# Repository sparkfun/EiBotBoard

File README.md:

EiBotBoard
==========

[*EiBotBoard (WIG-10025)*](https://www.sparkfun.com/products/10025)

The EiBotBoard (EBB) was originally designed for the Egg-Bot project. 
It is a small (2.2" x 2.2") two channel stepper motor driver board with USB microcontroller. 
It is based on the UBW board and supports all of the commands that the UBW does (for the most part), plus several extra, like stepper motor commands and RC servo output commands.

Repository Contents
-------------------
* **/Hardware** - All Eagle design files (.brd, .sch)
* **/Production** - Production panel files (.brd)

License Information
-------------------
Distributed as-is; no warranty is given.

_**Note:** This product is a collaboration with Brian Schmalz. A portion of each sales goes back to him for product support and continued development._

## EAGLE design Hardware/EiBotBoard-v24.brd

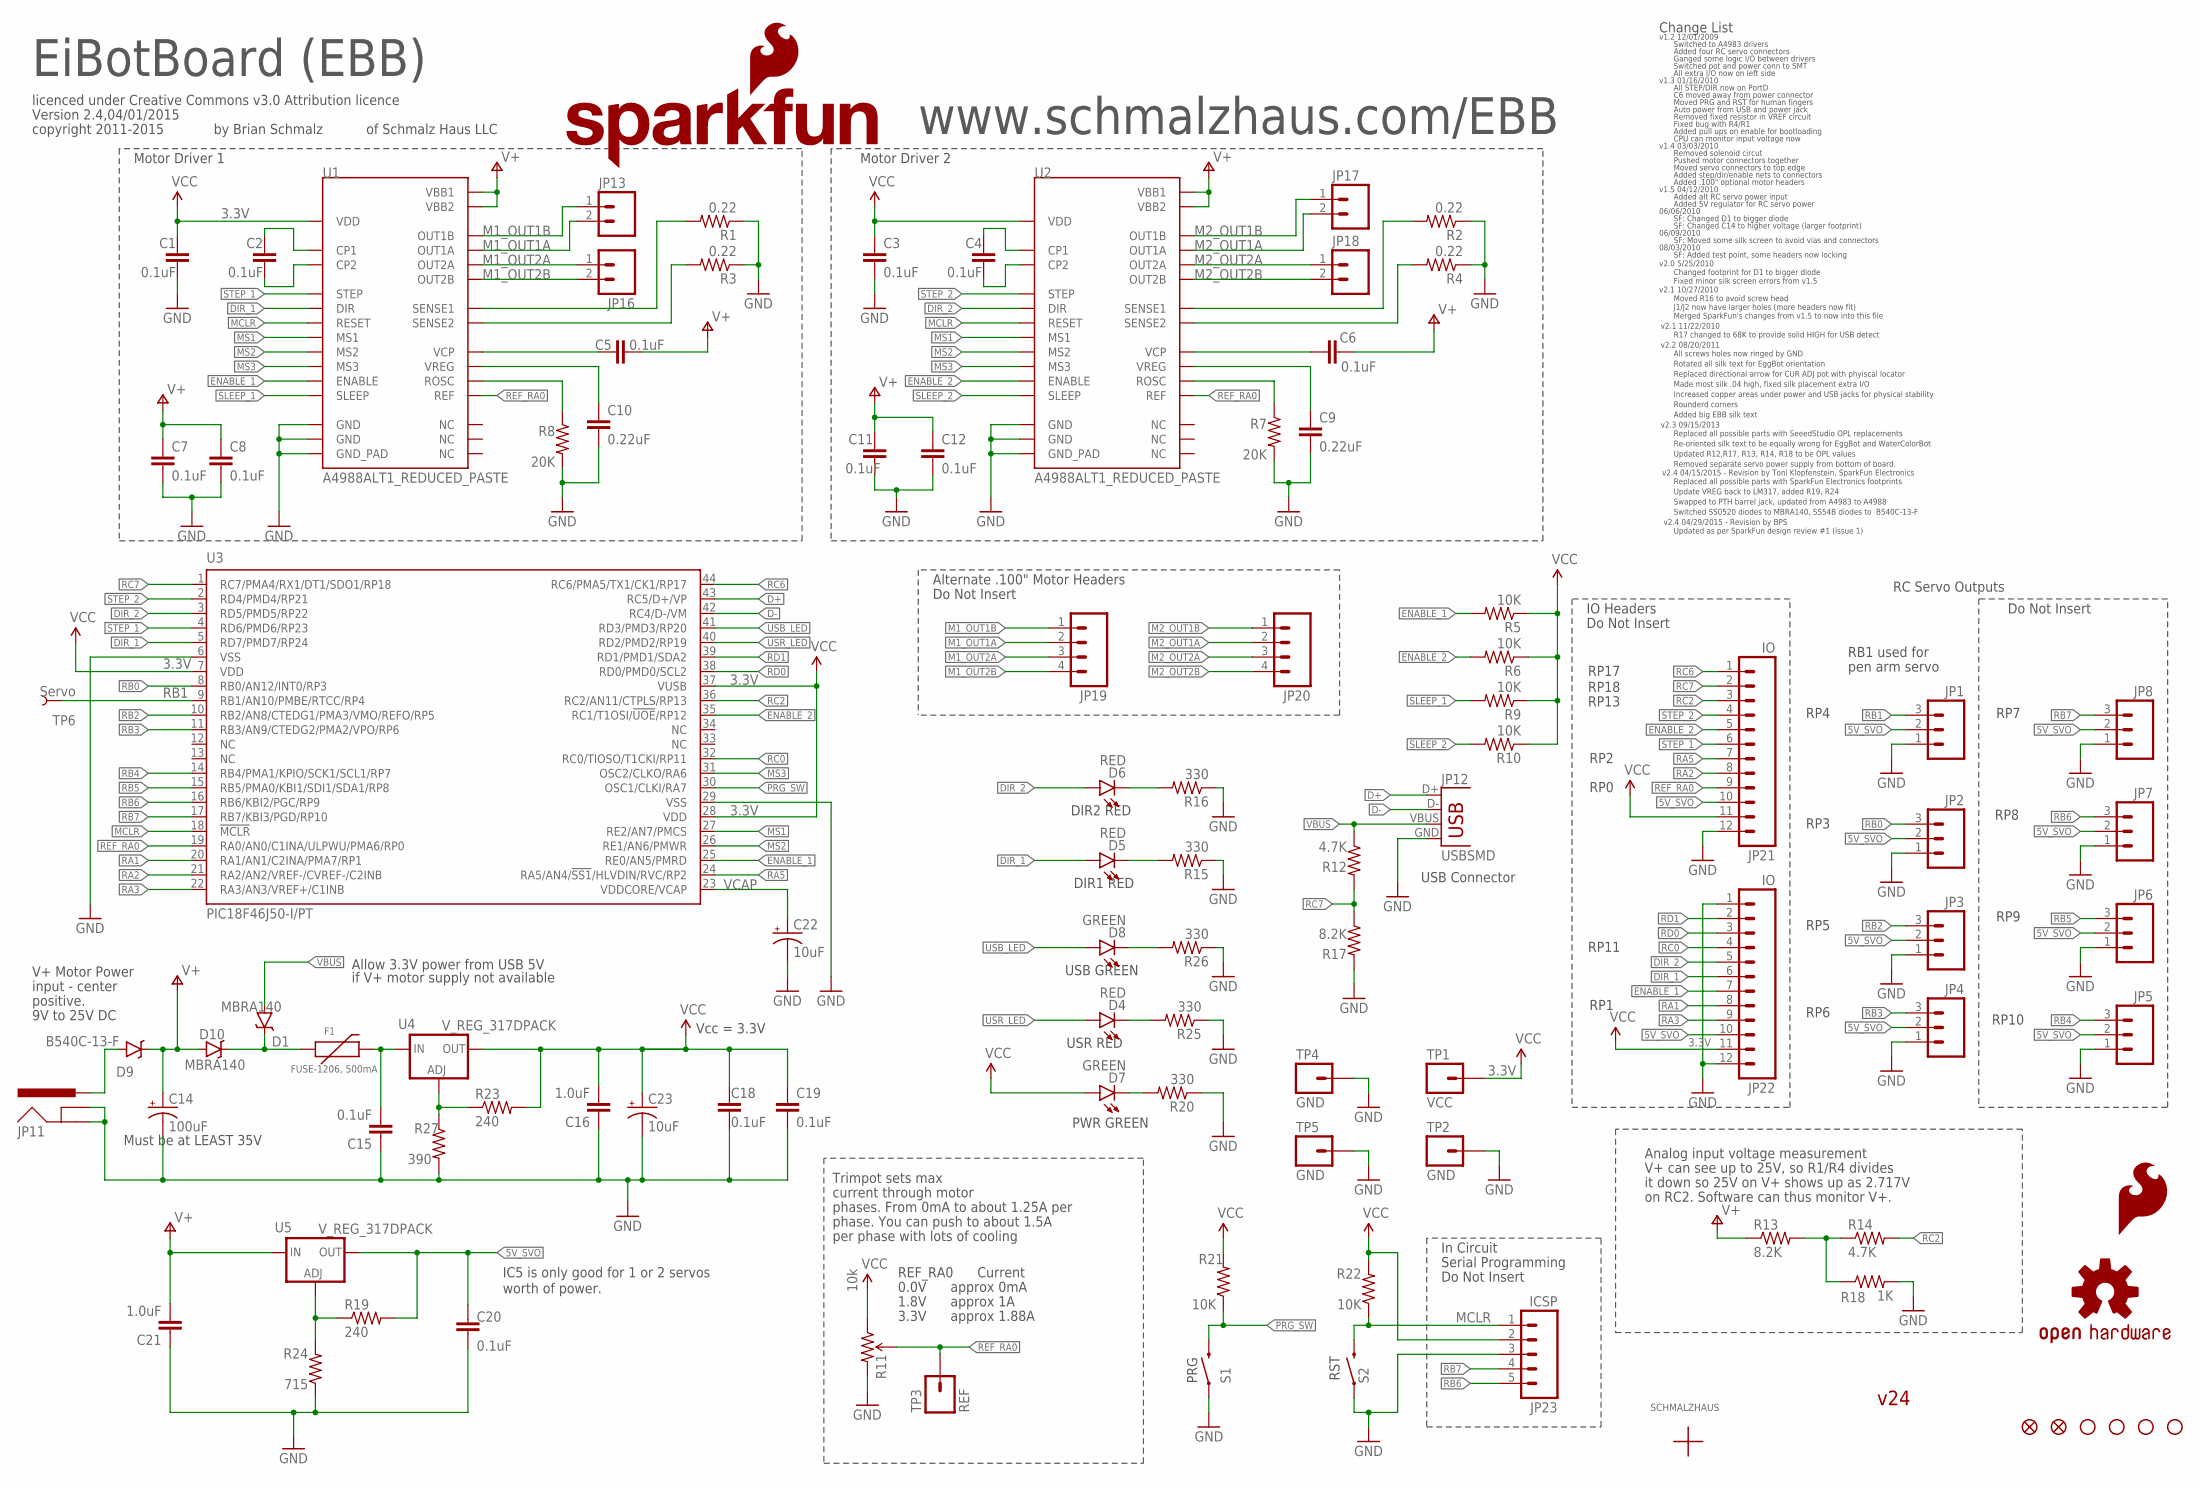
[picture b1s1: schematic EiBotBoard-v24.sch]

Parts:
C1, C2, C3, C4, C5, C6, C7, C8, C11, C12, C15, C18, C19, C20: 0.1uF; 0603-CAP
C9, C10: 0.22uF; 0603-CAP
C14: 100uF; NIC_10X10.5_CAP
C16, C21: 1.0uF; 0603-CAP
C22, C23: 10uF; EIA3528
D1, D10: MBRA140; SMA-DIODE
D4, D5, D6: RED; LED-0603
D7, D8: GREEN; LED-0603
D9: B540C-13-F; SMC
F1: FUSE-1206, 500mA; PTC-1206
JP1, JP2, JP3, JP4, JP5, JP6, JP7, JP8: M03LOCK_NO_SILK; 1X03_LOCK_NO_SILK
JP11: POWER_JACKPTH_LOCK; POWER_JACK_PTH_LOCK
JP12: USBSMD; USB-MINIB
JP13, JP16, JP17, JP18: M023.5MM_LOCK; SCREWTERMINAL-3.5MM-2_LOCK
JP14, JP15: FIDUCIAL1X2; FIDUCIAL-1X2
JP19, JP20: M04POLAR; MOLEX-1X4
JP21, JP22: IO; 1X12
JP23: ICSP; 1X05_NO_SILK
LOGO1: OSHW-LOGOS; OSHW-LOGO-S
LOGO2: SFE_LOGO_FLAME.2_INCH; SFE_LOGO_FLAME_.2
LOGO3: SFE_LOGO_NAME_FLAME.2_INCH; SFE_LOGO_NAME_FLAME_.2
R1, R2, R3, R4: 0.22; 0805
R5, R6, R9, R10, R21, R22: 10K; 0603-RES
R7, R8: 20K; 0603-RES
R11: 10k; TRIMPOT-3MM
R12, R14: 4.7K; 0603-RES
R13, R17: 8.2K; 0603-RES
R15, R16, R20, R25, R26: 330; 0603-RES
R18: 1K; 0603-RES
R19, R23: 240; 0603-RES
R24: 715; 0603-RES
R27: 390; 0603-RES
S1, S2: SWITCH-MOMENTARY-2SMD; TACTILE-SWITCH-SMD
TP1: VCC; 1X01_NOSILK
TP2, TP4, TP5: GND; 1X01_NOSILK
TP3: REF; 1X01
TP6: Servo; PAD.03X.05
U1, U2: A4988ALT1_REDUCED_PASTE; QFN-28-5MM_ALT1_REDUCED_PASTE
U3: PIC18F46J50-I/PT; TQFP44
U4, U5: V_REG_317DPACK; V-REG_DPACK
U$1: SCHMALZHAUSSCHMALZHAUS_SMALL; SCHMALZHAUS_SMALL
U$2, U$3, U$4, U$5: STAND-OFF

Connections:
3.3V: C1.1, C3.1, C16.2, C18.2, C19.2, C23.A (+), D7.A, JP21.11, JP22.11, JP23.2, R5.1, R6.1, R9.1, R10.1, R11.1 (CCW), R21.2, R22.2, R23.2, TP1.1, U1.P$15 (VDD), U2.P$15 (VDD), U3.7 (VDD), U3.28 (VDD), U3.37 (VUSB), U4.4 (OUT)
5V_SVO: C20.2, JP1.2, JP2.2, JP3.2, JP4.2, JP5.2, JP6.2, JP7.2, JP8.2, JP21.10, JP22.10, R19.2, U5.4 (OUT)
D+: JP12.D+, U3.43 (RC5/D+/VP)
D-: JP12.D-, U3.42 (RC4/D-/VM)
DIR_1: D5.A, JP22.6, U1.P$19 (DIR), U3.5 (RD7/PMD7/RP24)
DIR_2: D6.A, JP22.5, U2.P$19 (DIR), U3.3 (RD5/PMD5/RP22)
ENABLE_1: JP22.7, R5.2, U1.P$2 (ENABLE), U3.25 (RE0/AN5/PMRD)
ENABLE_2: JP21.5, R6.2, U2.P$2 (ENABLE), U3.35 (RC1/T1OSI/!UOE!/RP12)
GND: C1.2, C3.2, C7.2, C8.2, C9.2, C10.2, C11.2, C12.2, C14.-, C15.1, C16.1, C18.1, C19.1, C20.1, C21.1, C22.C (-), C23.C (-), JP1.1, JP2.1, JP3.1, JP4.1, JP5.1, JP6.1, JP7.1, JP8.1, JP11.GND, JP11.GNDBREAK, JP12.GND, JP21.12, JP22.1, JP22.12, JP23.3, R1.1, R2.1, R3.1, R4.1, R7.2, R8.2, R11.3 (CW), R15.1, R16.1, R17.2, R18.2, R20.1, R24.1, R25.1, R26.1, R27.2, S1.1, S2.1, TP2.1, TP4.1, TP5.1, U1.P$3 (GND), U1.P$18 (GND), U1.P$29 (GND_PAD), U2.P$3 (GND), U2.P$18 (GND), U2.P$29 (GND_PAD), U3.6 (VSS), U3.29 (VSS)
M1_OUT1A: JP13.2, JP19.2, U1.P$24 (OUT1A)
M1_OUT1B: JP13.1, JP19.1, U1.P$21 (OUT1B)
M1_OUT2A: JP16.1, JP19.3, U1.P$26 (OUT2A)
M1_OUT2B: JP16.2, JP19.4, U1.P$1 (OUT2B)
M2_OUT1A: JP17.2, JP20.2, U2.P$24 (OUT1A)
M2_OUT1B: JP17.1, JP20.1, U2.P$21 (OUT1B)
M2_OUT2A: JP18.1, JP20.3, U2.P$26 (OUT2A)
M2_OUT2B: JP18.2, JP20.4, U2.P$1 (OUT2B)
MCLR: JP23.1, R22.1, S2.3 (2), U1.P$12 (RESET), U2.P$12 (RESET), U3.18 (!MCLR!)
MS1: U1.P$9 (MS1), U2.P$9 (MS1), U3.27 (RE2/AN7/PMCS)
MS2: U1.P$10 (MS2), U2.P$10 (MS2), U3.26 (RE1/AN6/PMWR)
MS3: U1.P$11 (MS3), U2.P$11 (MS3), U3.31 (OSC2/CLKO/RA6)
unnamed: D6.C, R16.2
unnamed: D1.C, D10.C, F1.1
unnamed: C2.1, U1.P$4 (CP1)
unnamed: R13.2, R14.1, R18.1
unnamed: C2.2, U1.P$5 (CP2)
unnamed: D9.A, JP11.PWR
unnamed: D5.C, R15.2
unnamed: D8.C, R26.2
unnamed: R23.1, R27.1, U4.1 (ADJ)
unnamed: D4.C, R25.2
unnamed: D7.C, R20.2
unnamed: R19.1, R24.2, U5.1 (ADJ)
unnamed: C4.1, U2.P$4 (CP1)
unnamed: C4.2, U2.P$5 (CP2)
unnamed: R8.1, U1.P$13 (ROSC)
unnamed: C10.1, U1.P$8 (VREG)
unnamed: C5.1, U1.P$6 (VCP)
unnamed: R3.2, U1.P$27 (SENSE2)
unnamed: R1.2, U1.P$23 (SENSE1)
unnamed: C15.2, F1.2, U4.3 (IN)
unnamed: C6.1, U2.P$6 (VCP)
unnamed: R2.2, U2.P$23 (SENSE1)
unnamed: R4.2, U2.P$27 (SENSE2)
unnamed: C9.1, U2.P$8 (VREG)
unnamed: R7.1, U2.P$13 (ROSC)
PRG_SW: R21.1, S1.3 (2), U3.30 (OSC1/CLKI/RA7)
RA1: JP22.8, U3.20 (RA1/AN1/C2INA/PMA7/RP1)
RA2: JP21.8, U3.21 (RA2/AN2/VREF-/CVREF-/C2INB)
RA3: JP22.9, U3.22 (RA3/AN3/VREF+/C1INB)
RA5: JP21.7, U3.24 (RA5/AN4/!SS1!/HLVDIN/RVC/RP2)
RB0: JP2.3, U3.8 (RB0/AN12/INT0/RP3)
RB1: JP1.3, TP6.P$1, U3.9 (RB1/AN10/PMBE/RTCC/RP4)
RB2: JP3.3, U3.10 (RB2/AN8/CTEDG1/PMA3/VMO/REFO/RP5)
RB3: JP4.3, U3.11 (RB3/AN9/CTEDG2/PMA2/VPO/RP6)
RB4: JP5.3, U3.14 (RB4/PMA1/KPIO/SCK1/SCL1/RP7)
RB5: JP6.3, U3.15 (RB5/PMA0/KBI1/SDI1/SDA1/RP8)
RB6: JP7.3, JP23.5, U3.16 (RB6/KBI2/PGC/RP9)
RB7: JP8.3, JP23.4, U3.17 (RB7/KBI3/PGD/RP10)
RC0: JP22.4, U3.32 (RC0/TIOSO/T1CKI/RP11)
RC2: JP21.3, R14.2, U3.36 (RC2/AN11/CTPLS/RP13)
RC6: JP21.1, U3.44 (RC6/PMA5/TX1/CK1/RP17)
RC7: JP21.2, R12.2, R17.1, U3.1 (RC7/PMA4/RX1/DT1/SDO1/RP18)
RD0: JP22.3, U3.38 (RD0/PMD0/SCL2)
RD1: JP22.2, U3.39 (RD1/PMD1/SDA2)
REF_RA0: JP21.9, R11.2 (WIPER), TP3.1, U1.P$17 (REF), U2.P$17 (REF), U3.19 (RA0/AN0/C1INA/ULPWU/PMA6/RP0)
SLEEP_1: R9.2, U1.P$14 (SLEEP)
SLEEP_2: R10.2, U2.P$14 (SLEEP)
STEP_1: JP21.6, U1.P$16 (STEP), U3.4 (RD6/PMD6/RP23)
STEP_2: JP21.4, U2.P$16 (STEP), U3.2 (RD4/PMD4/RP21)
USB_LED: D8.A, U3.41 (RD3/PMD3/RP20)
USR_LED: D4.A, U3.40 (RD2/PMD2/RP19)
V+: C5.2, C6.2, C7.1, C8.1, C11.1, C12.1, C14.+, C21.2, D9.C, D10.A, R13.1, U1.P$22 (VBB1), U1.P$28 (VBB2), U2.P$22 (VBB1), U2.P$28 (VBB2), U5.3 (IN)
VBUS: D1.A, JP12.VBUS, R12.1
VCAP: C22.A (+), U3.23 (VDDCORE/VCAP)

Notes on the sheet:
EiBotBoard (EBB)
v1.2 12/01/2009
by Brian Schmalz
of Schmalz Haus LLC
www.schmalzhaus.com/EBB
licenced under Creative Commons v3.0 Attribution licence
PWR GREEN
DIR1 RED
DIR2 RED
USR RED
USB GREEN
PRG
RST
RP17
RP18
Change List
Switched to A4983 drivers
Added four RC servo connectors
Ganged some logic I/O between drivers
Switched pot and power conn to SMT
All extra I/O now on left side
Vcc = 3.3V
v1.3 01/16/2010
All STEP/DIR now on PortD
C6 moved away from power connector
Moved PRG and RST for human fingers
Auto power from USB and power jack
Removed fixed resistor in VREF circuit
Fixed bug with R4/R1
CPU can monitor input voltage now
Added pull ups on enable for bootloading
V+ can see up to 25V, so R1/R4 divides
it down so 25V on V+ shows up as 2.717V
Analog input voltage measurement
on RC2. Software can thus monitor V+.
RP11
Version 2.4,04/01/2015
v1.4 03/03/2010
Removed solenoid circut
Pushed motor connectors together

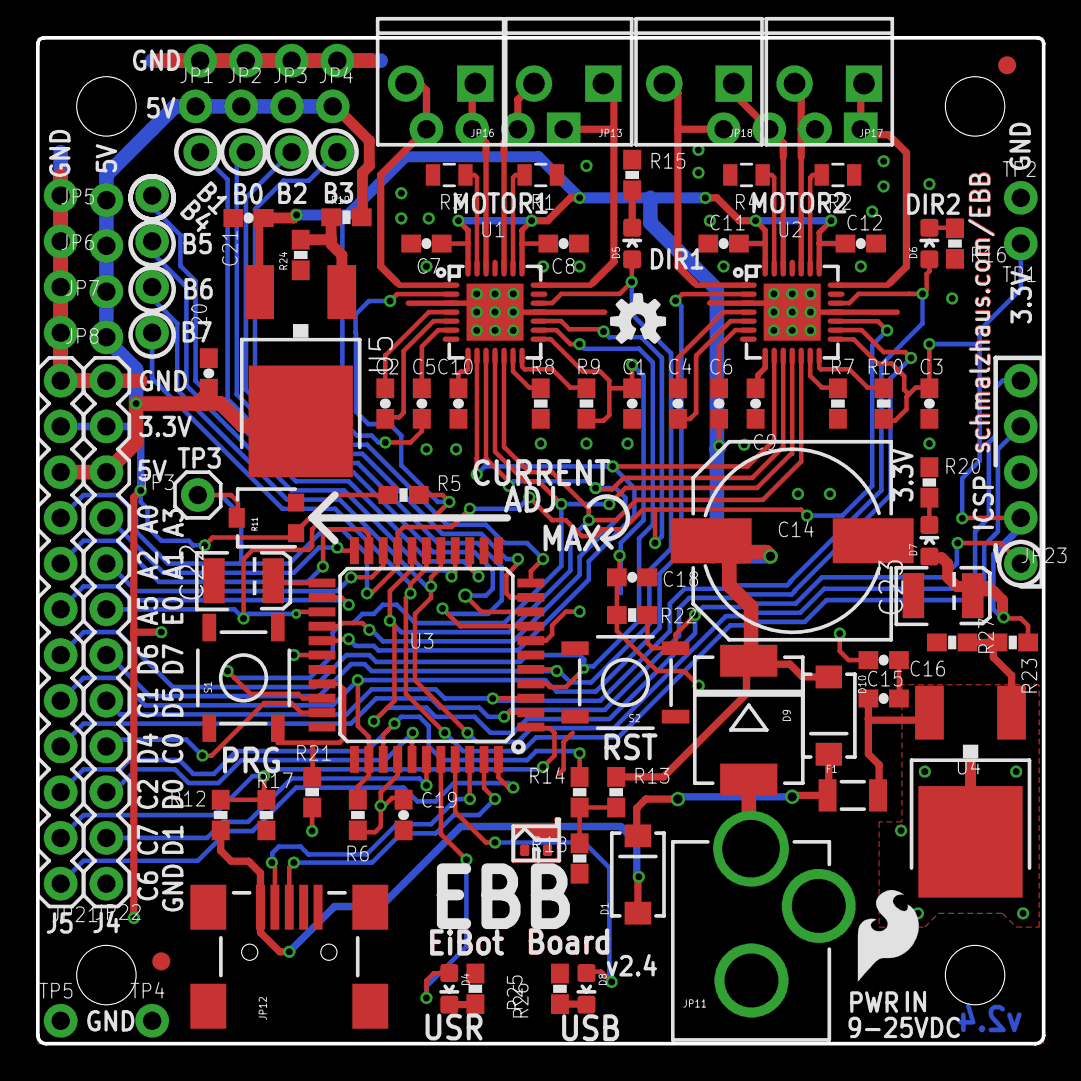
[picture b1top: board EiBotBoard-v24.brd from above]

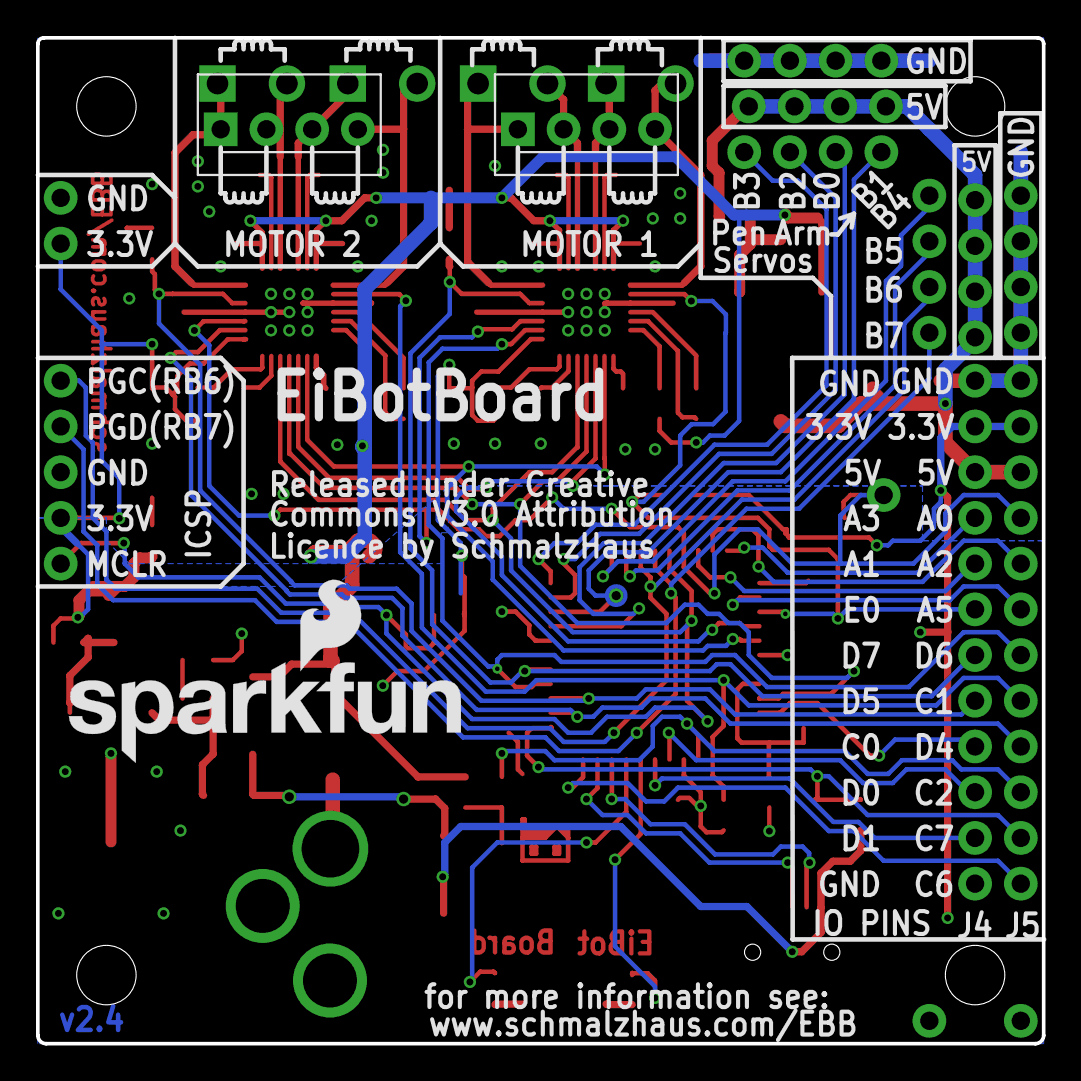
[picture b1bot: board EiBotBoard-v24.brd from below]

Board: 2 copper layers, 55.9 x 55.9 mm, 99 parts (4 on the bottom side), 75 nets.

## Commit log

2015-03-10 Adding hardware files, updating README
2015-03-31 Version 2.3 from Schmalz Haus. This is the latest version that is in production at SeeedStudios (EMSL) and is shipping with EggBot and WatercolorBot. See changes.txt and schematic for list of changes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
2015-04-02 Updating part numbers to SFE libraries, swapping vregs
2015-04-02 Adding production directory
2015-04-03 Updating to A4988 ICs
2015-04-03 Updating additional packages, fixing DRC errors
2015-04-03 Adding dimension measures, license info and designer names to brd files
2015-04-17 Updating to version 2.4
2015-04-17 Removing v_23 files
2015-04-30 Updated board and schematic as per Peter Lewis' design review nodes (issue #1 in GitHub)
2015-05-01 Reverted LEDs back to their original colors, removed outline line on tPlace, made outline on dimension layer 0.008" wide, switched driver chip footprints to A4988ALT1_REDUCED_PASTE.
2015-05-02 Added MAX direction indication on top silk for current adjust pot.
2015-05-20 Pushing BOM update

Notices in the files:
Hardware/EiBotBoard-v24.brd:
Licensed under Creative Commons v3.0 Attribution License
Hardware/EiBotBoard-v24.sch:
copyright 2011-2015
parts and their libraries:
SparkFun-Capacitors: Licensing: Creative Commons ShareAlike 4.0 International - https://creativecommons.org/licenses/by-sa/4.0
